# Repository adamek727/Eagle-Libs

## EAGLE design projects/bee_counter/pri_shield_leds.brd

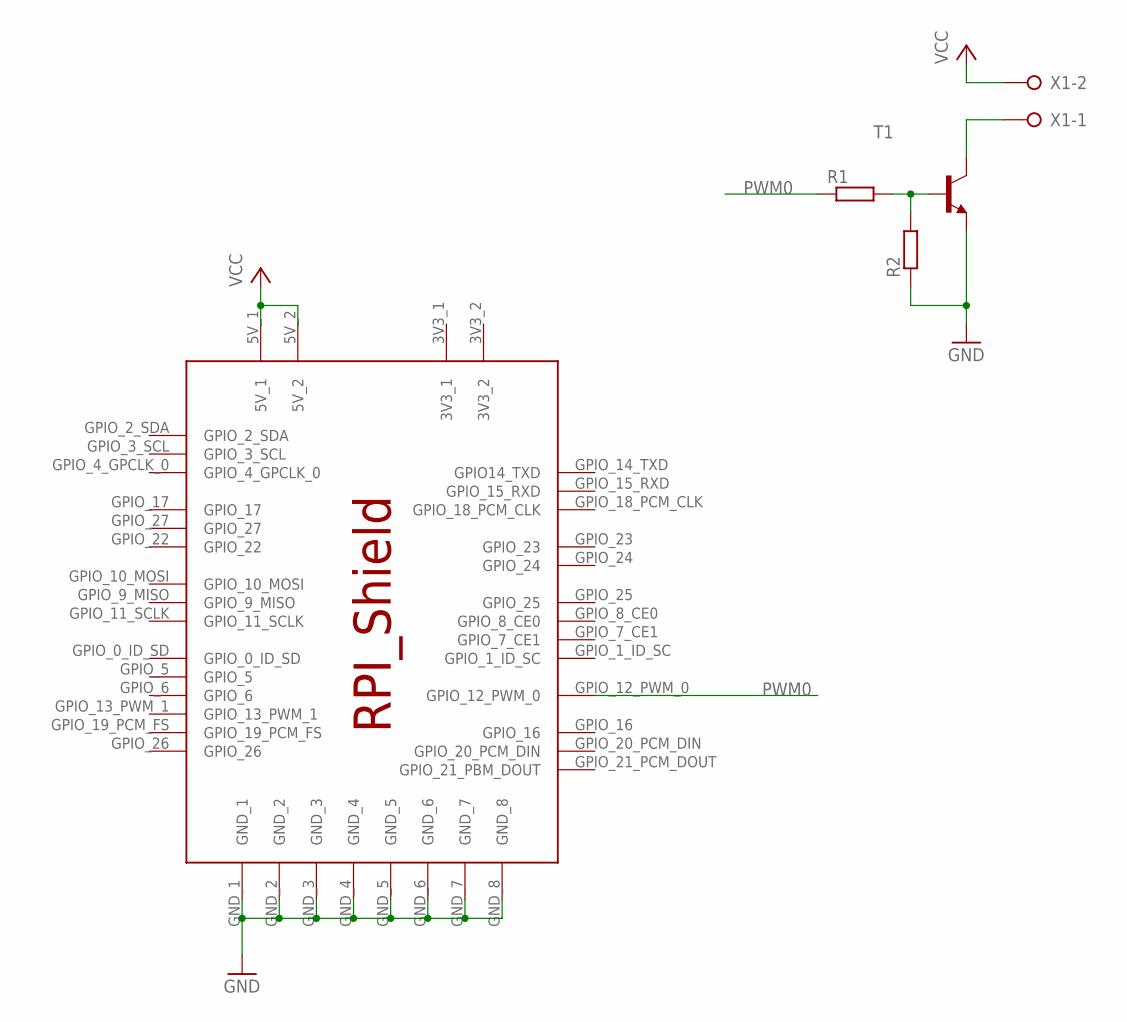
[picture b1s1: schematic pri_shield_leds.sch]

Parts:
R1, R2: R-EU_R1206; R1206
T1: -NPN-SOT223; SOT223
U$1: RPI_SHIELD
X1: W237-02P; W237-132

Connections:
GND: R2.1, T1.3 (E), U$1.GND_1, U$1.GND_2, U$1.GND_3, U$1.GND_4, U$1.GND_5, U$1.GND_6, U$1.GND_7, U$1.GND_8
unnamed: T1.4 (C), X1.1
unnamed: R1.2, R2.2, T1.1 (B)
PWM0: R1.1, U$1.GPIO_12_PWM_0
VCC: U$1.5V_1, U$1.5V_2, X1.2

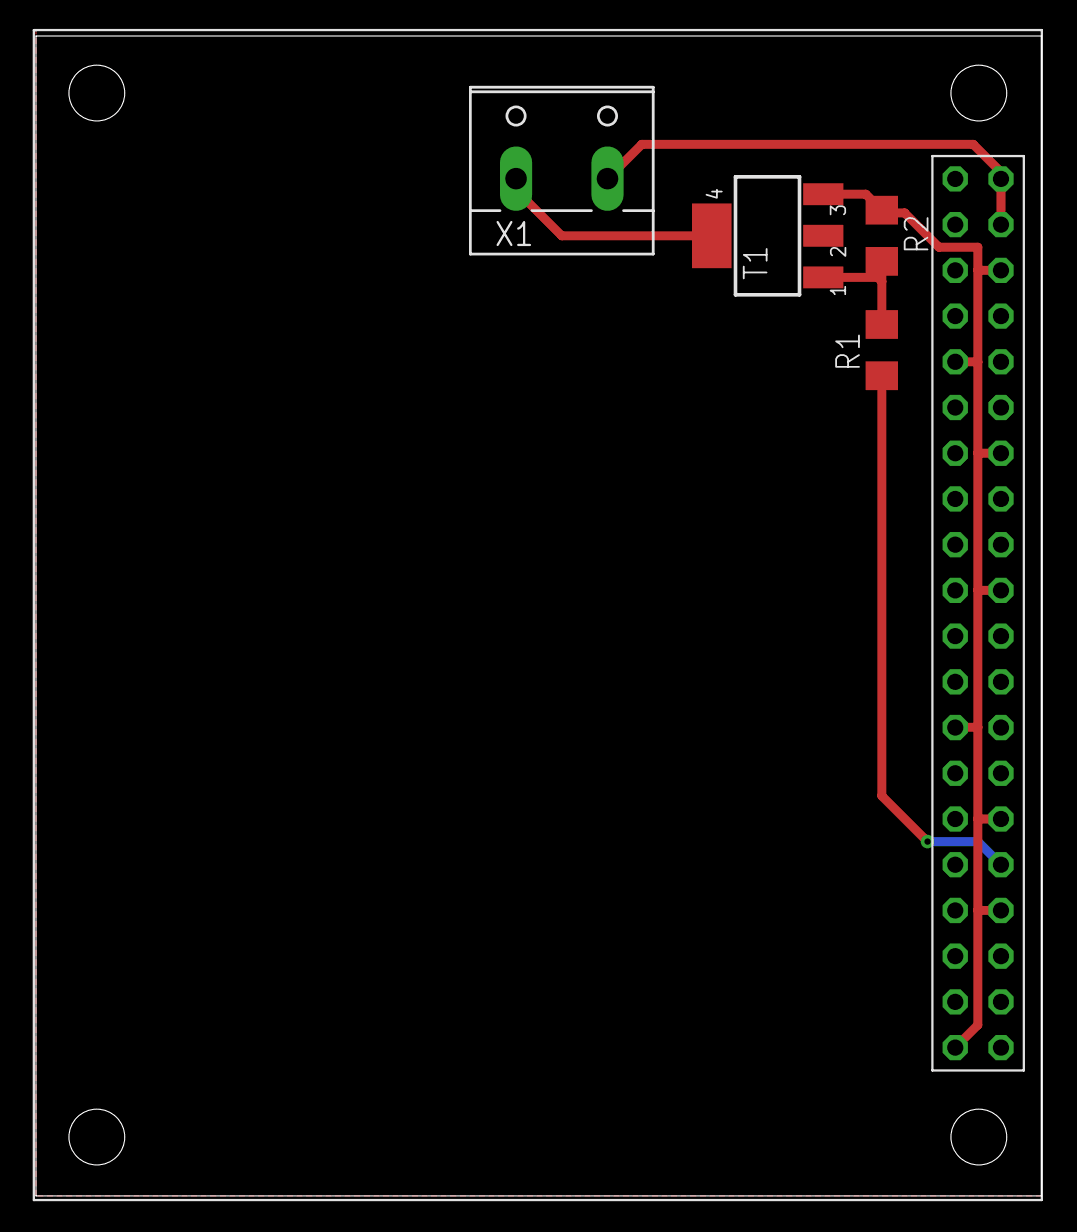
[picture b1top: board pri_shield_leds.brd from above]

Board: 2 copper layers, 55.9 x 64.4 mm, 5 parts (0 on the bottom side), 5 nets.

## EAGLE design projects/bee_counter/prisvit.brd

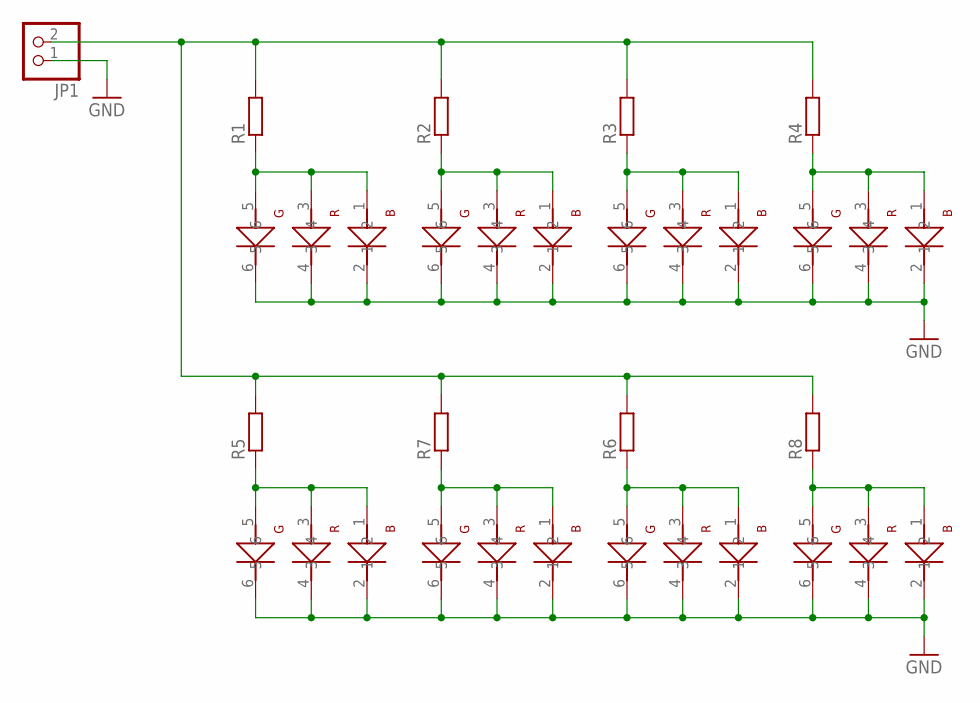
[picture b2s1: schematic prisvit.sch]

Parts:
JP1: PINHD-1X2; 1X02
R1, R2, R3, R4, R5, R6, R7, R8: R-EU_M2012; M2012
U$1, U$2, U$3, U$4, U$5, U$6, U$7, U$8: 5050_LED

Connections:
GND: JP1.1, U$1.2, U$1.4, U$1.6, U$2.2, U$2.4, U$2.6, U$3.2, U$3.4, U$3.6, U$4.2, U$4.4, U$4.6, U$5.2, U$5.4, U$5.6, U$6.2, U$6.4, U$6.6, U$7.2, U$7.4, U$7.6, U$8.2, U$8.4, U$8.6
unnamed: JP1.2, R1.2, R2.2, R3.2, R4.2, R5.2, R6.2, R7.2, R8.2
unnamed: R4.1, U$6.1, U$6.3, U$6.5
unnamed: R3.1, U$4.1, U$4.3, U$4.5
unnamed: R2.1, U$3.1, U$3.3, U$3.5
unnamed: R1.1, U$2.1, U$2.3, U$2.5
unnamed: R5.1, U$8.1, U$8.3, U$8.5
unnamed: R7.1, U$1.1, U$1.3, U$1.5
unnamed: R6.1, U$5.1, U$5.3, U$5.5
unnamed: R8.1, U$7.1, U$7.3, U$7.5

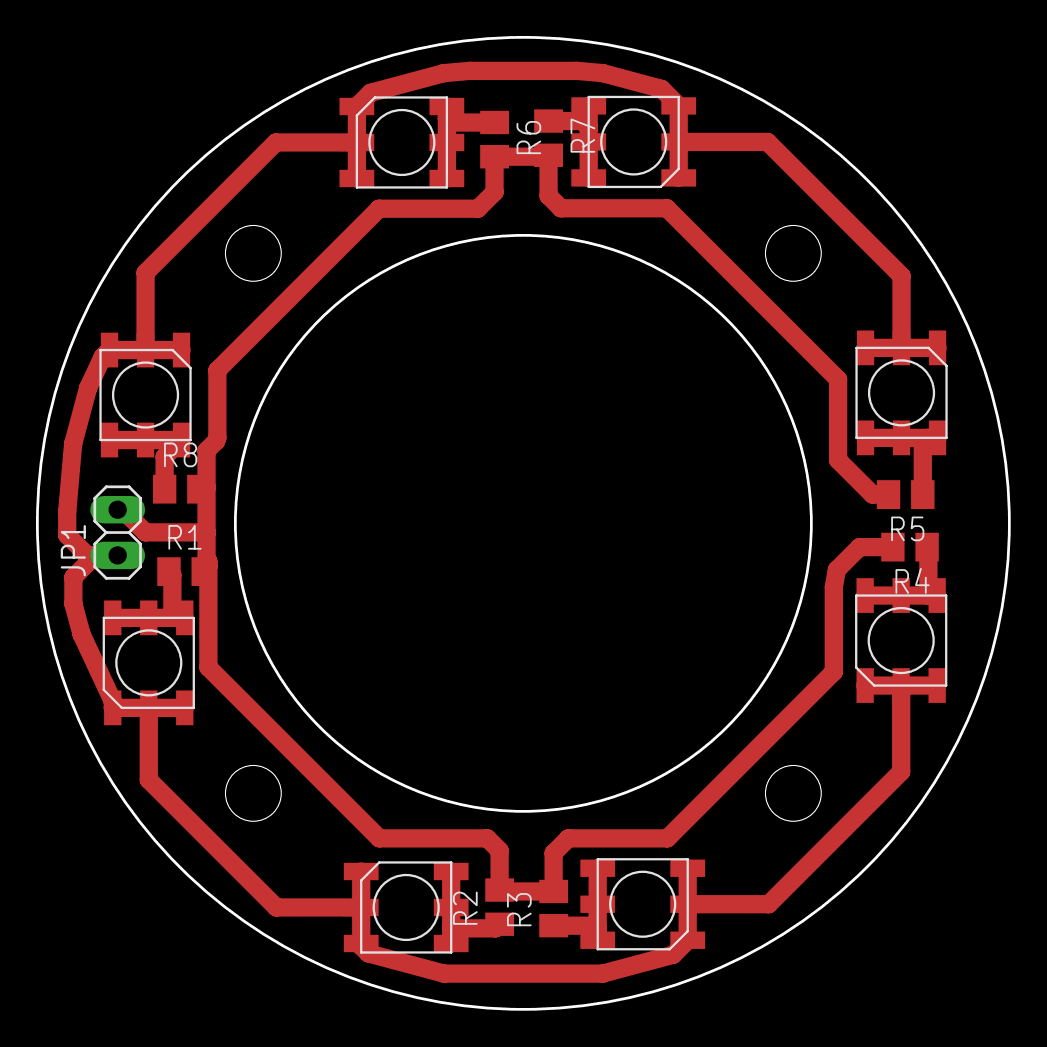
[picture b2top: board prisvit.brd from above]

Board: 2 copper layers, 54.0 x 54.0 mm, 17 parts (0 on the bottom side), 10 nets.

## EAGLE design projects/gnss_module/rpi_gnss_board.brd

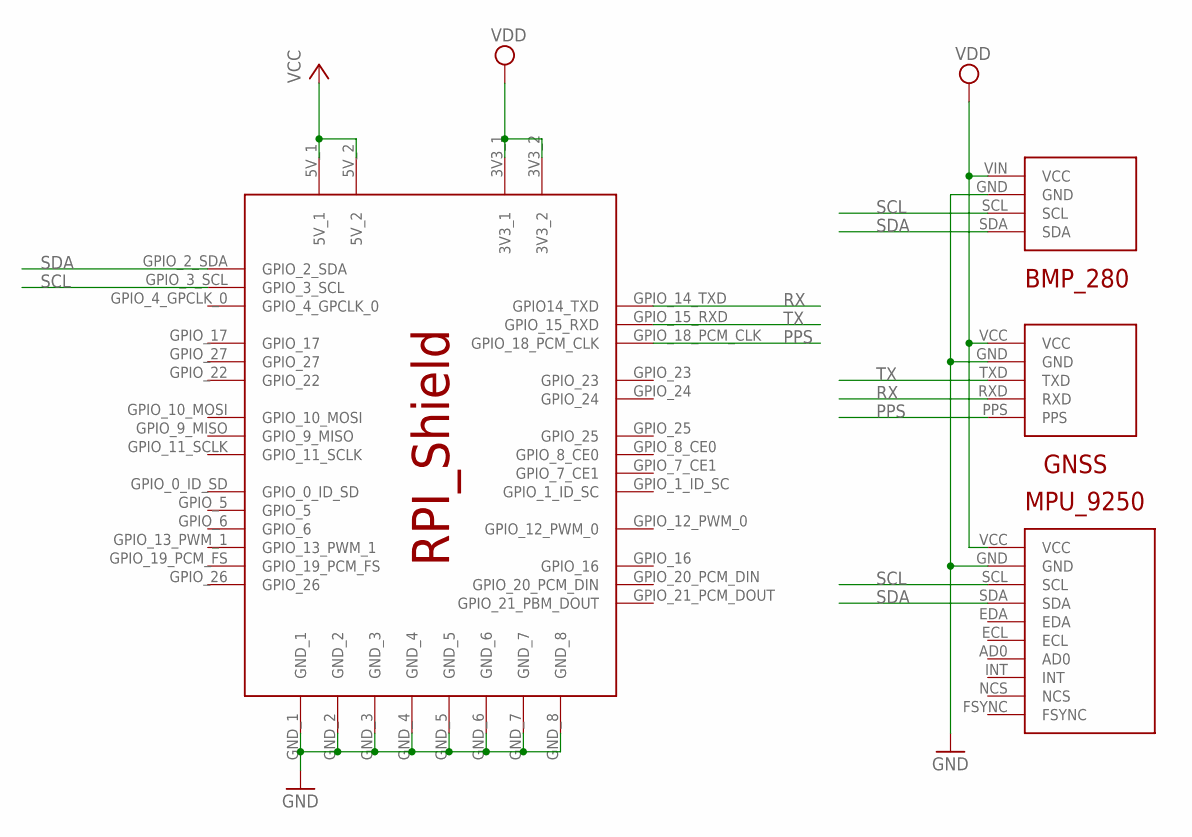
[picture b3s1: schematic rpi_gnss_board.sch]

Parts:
U$1: RPI_SHIELD
U$2: BMP_280
U$3: GNSS_MODULE_UBLOX
U$4: MPU_9250

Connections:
GND: U$1.GND_1, U$1.GND_2, U$1.GND_3, U$1.GND_4, U$1.GND_5, U$1.GND_6, U$1.GND_7, U$1.GND_8, U$2.GND, U$3.GND, U$4.GND
PPS: U$1.GPIO_18_PCM_CLK, U$3.PPS
RX: U$1.GPIO_14_TXD (GPIO14_TXD), U$3.RXD
SCL: U$1.GPIO_3_SCL, U$2.SCL, U$4.SCL
SDA: U$1.GPIO_2_SDA, U$2.SDA, U$4.SDA
TX: U$1.GPIO_15_RXD, U$3.TXD
VCC: U$1.5V_1, U$1.5V_2
VDD: U$1.3V3_1, U$1.3V3_2, U$2.VIN (VCC), U$3.VCC, U$4.VCC

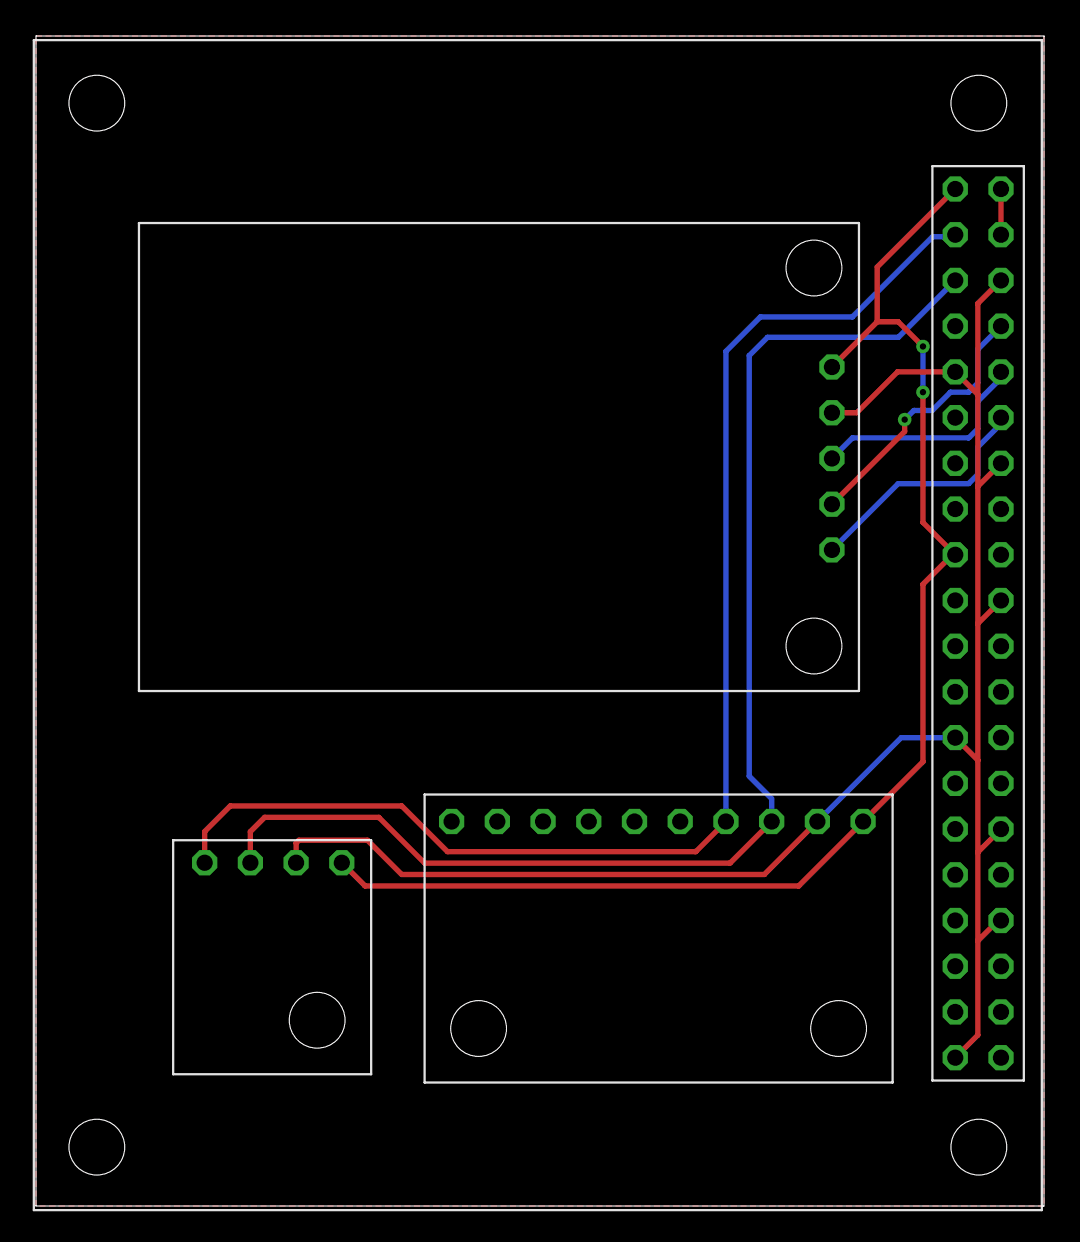
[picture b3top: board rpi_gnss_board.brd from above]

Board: 2 copper layers, 56.0 x 65.0 mm, 4 parts (0 on the bottom side), 8 nets.

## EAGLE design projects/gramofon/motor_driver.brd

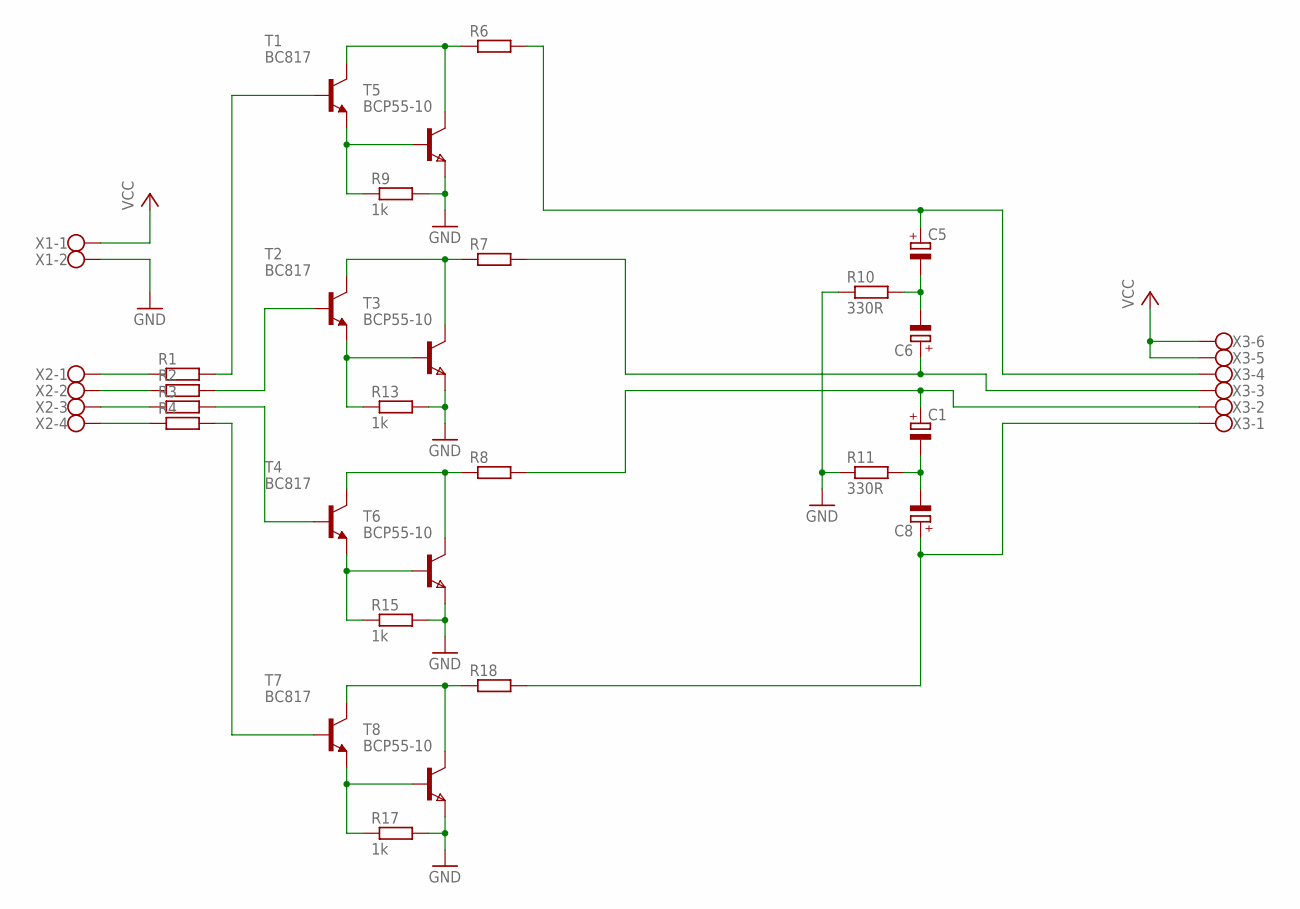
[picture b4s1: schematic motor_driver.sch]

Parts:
C1, C5, C6, C8: CPOL-EU153CLV-0807; 153CLV-0807
R1, R2, R3, R4: R-EU_M1206; M1206
R6, R7, R8, R18: R-EU_0922/22; 0922/22
R9, R13, R15, R17: 1k; M1206
R10, R11: 330R; M1206
T1, T2, T4, T7: BC817; SOT23-BEC
T3, T5, T6, T8: BCP55-10; SOT223
X1: W237-102
X2: W237-4
X3: W237-6

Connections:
GND: R9.2, R10.1, R11.1, R13.2, R15.2, R17.2, T3.3 (E), T5.3 (E), T6.3 (E), T8.3 (E), X1.2
unnamed: R1.1, X2.1
unnamed: R2.1, X2.2
unnamed: R3.1, X2.3
unnamed: R4.1, X2.4
unnamed: R1.2, T1.B
unnamed: C1.-, C8.-, R11.2
unnamed: R9.1, T1.E, T5.1 (B)
unnamed: R6.1, T1.C, T5.2 (C), T5.4 (C)
unnamed: C6.+, R7.2, X3.3
unnamed: C5.+, R6.2, X3.4
unnamed: C5.-, C6.-, R10.2
unnamed: R2.2, T2.B
unnamed: R13.1, T2.E, T3.1 (B)
unnamed: R7.1, T2.C, T3.2 (C), T3.4 (C)
unnamed: R3.2, T4.B
unnamed: R15.1, T4.E, T6.1 (B)
unnamed: R8.1, T4.C, T6.2 (C), T6.4 (C)
unnamed: C1.+, R8.2, X3.2
unnamed: R4.2, T7.B
unnamed: R17.1, T7.E, T8.1 (B)
unnamed: R18.1, T7.C, T8.2 (C), T8.4 (C)
unnamed: C8.+, R18.2, X3.1
VCC: X1.1, X3.5, X3.6

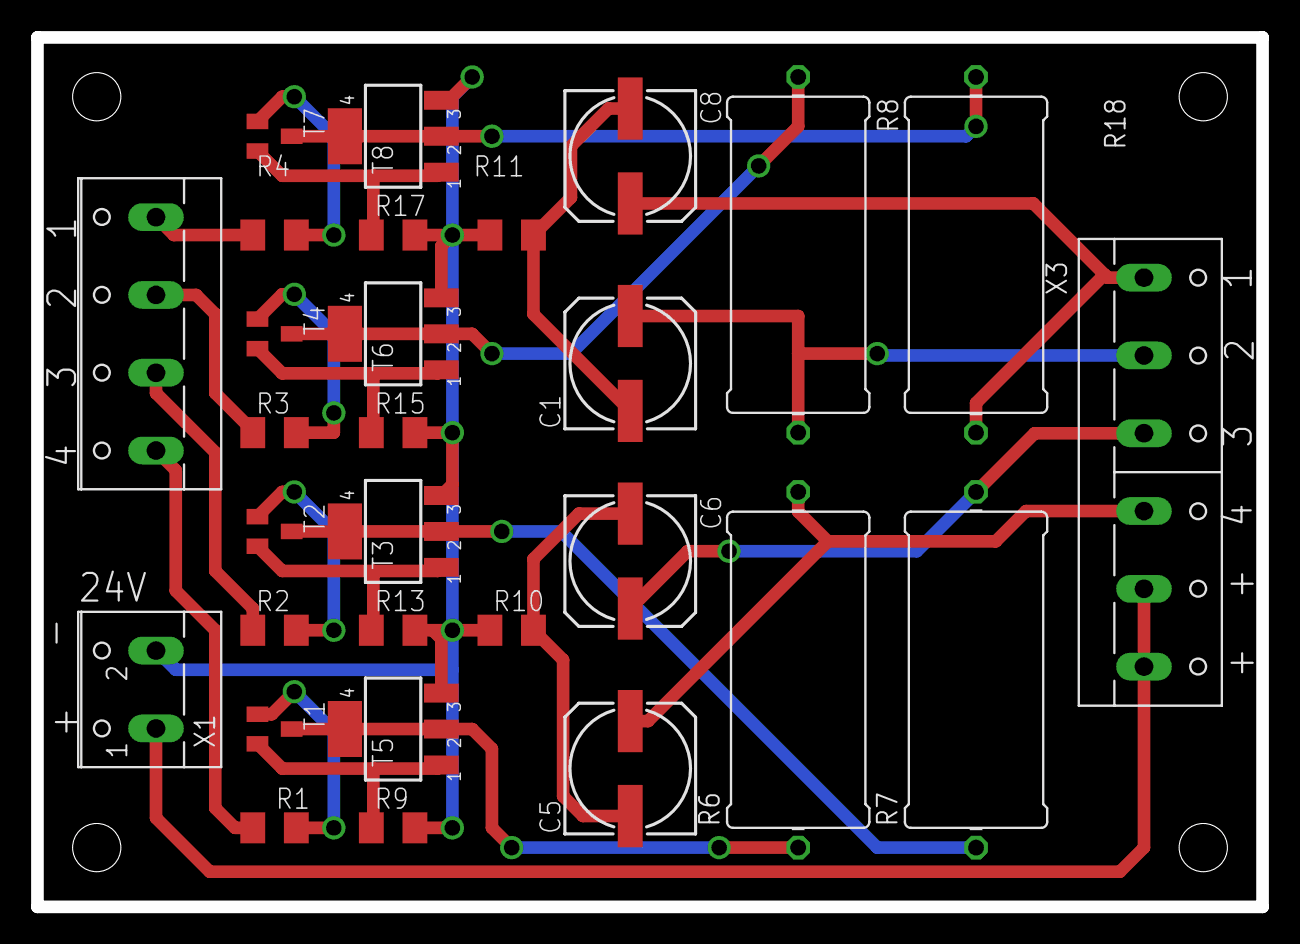
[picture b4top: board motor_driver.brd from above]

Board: 2 copper layers, 78.7 x 55.9 mm, 29 parts (0 on the bottom side), 24 nets.

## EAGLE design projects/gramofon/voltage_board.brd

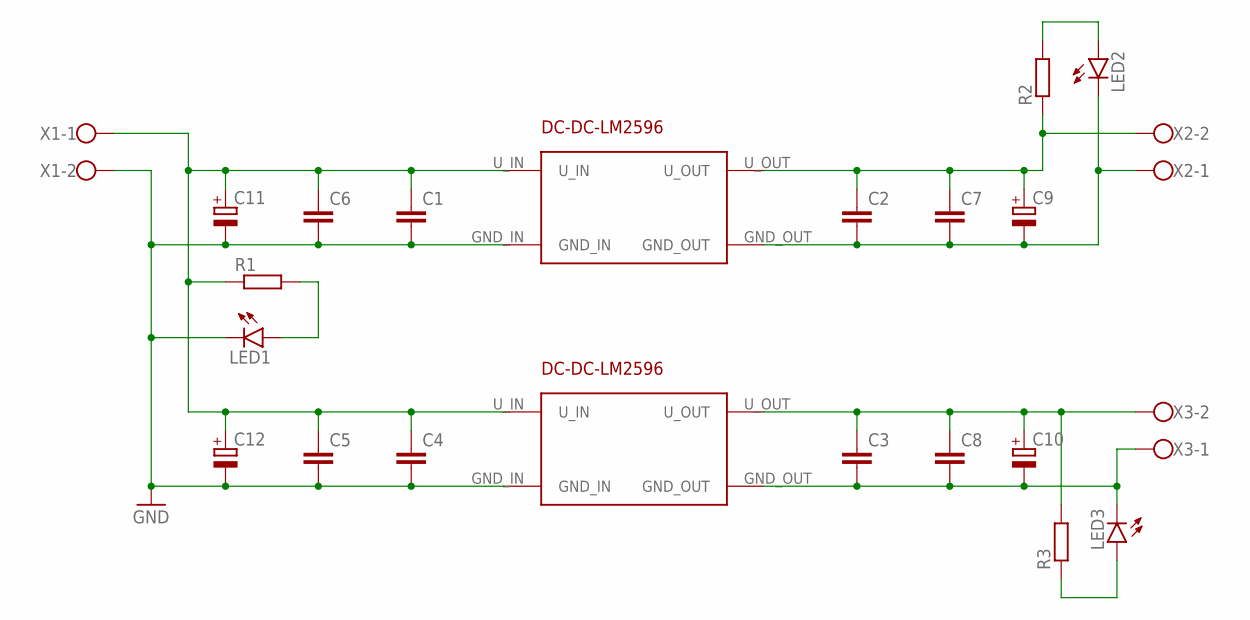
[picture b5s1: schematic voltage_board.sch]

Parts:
C1, C2, C3, C4, C5, C6, C7, C8: C-EUC1206; C1206
C9, C10, C11, C12: CPOL-EU140CLH-0810; 140CLH-0810
LED1, LED2, LED3: LEDSML1206; SML1206
R1, R2, R3: R-EU_M1206; M1206
U$1, U$2: DC-DC-LM2596
X1, X2, X3: W237-102

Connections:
GND: C1.2, C4.2, C5.2, C6.2, C11.-, C12.-, LED1.C, U$1.GND_IN, U$2.GND_IN, X1.2
unnamed: LED1.A, R1.2
unnamed: C3.2, C8.2, C10.-, LED3.C, U$2.GND_OUT, X3.1
unnamed: LED2.A, R2.2
unnamed: C3.1, C8.1, C10.+, R3.2, U$2.U_OUT, X3.2
unnamed: C1.1, C4.1, C5.1, C6.1, C11.+, C12.+, R1.1, U$1.U_IN, U$2.U_IN, X1.1
unnamed: C2.2, C7.2, C9.-, LED2.C, U$1.GND_OUT, X2.1
unnamed: C2.1, C7.1, C9.+, R2.1, U$1.U_OUT, X2.2
unnamed: LED3.A, R3.1

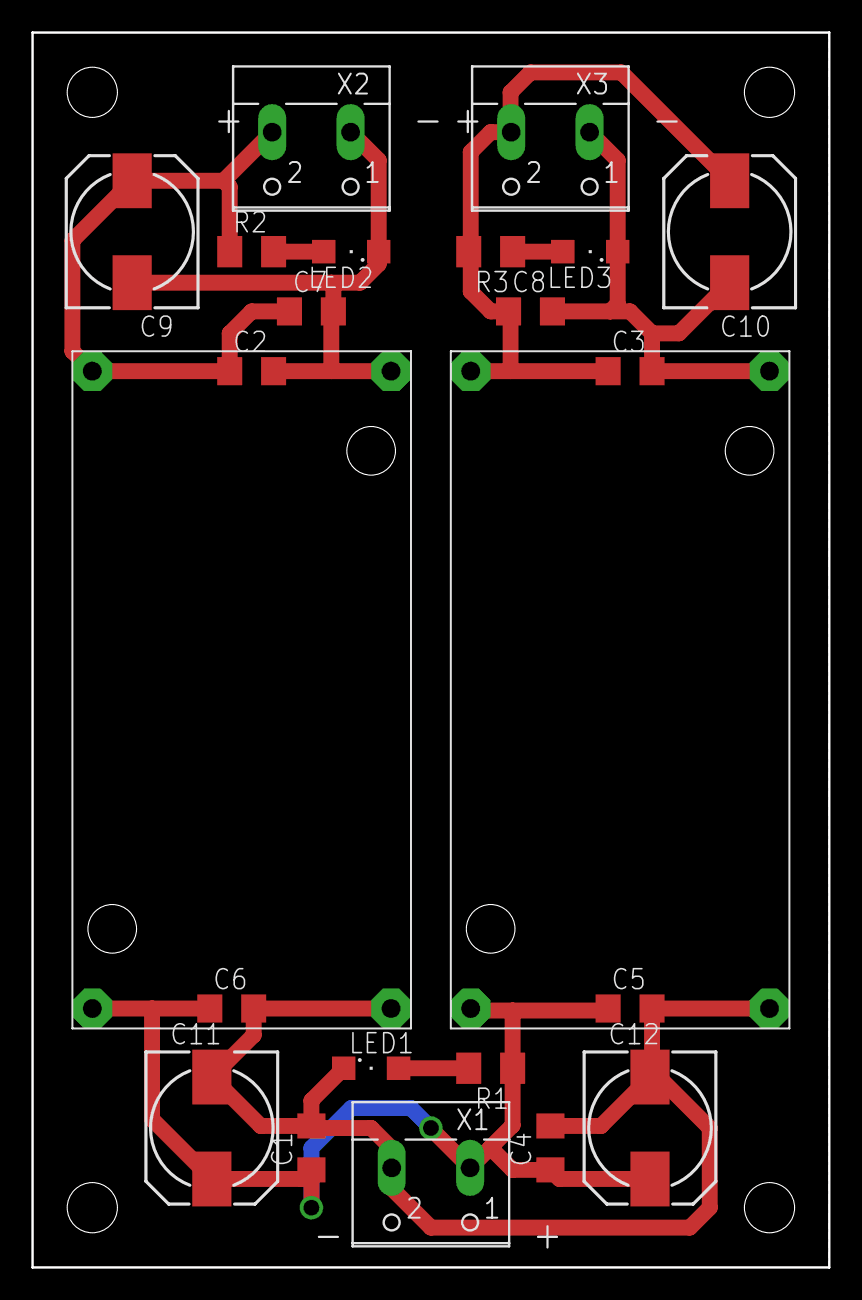
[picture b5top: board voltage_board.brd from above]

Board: 2 copper layers, 50.8 x 78.7 mm, 23 parts (0 on the bottom side), 9 nets.

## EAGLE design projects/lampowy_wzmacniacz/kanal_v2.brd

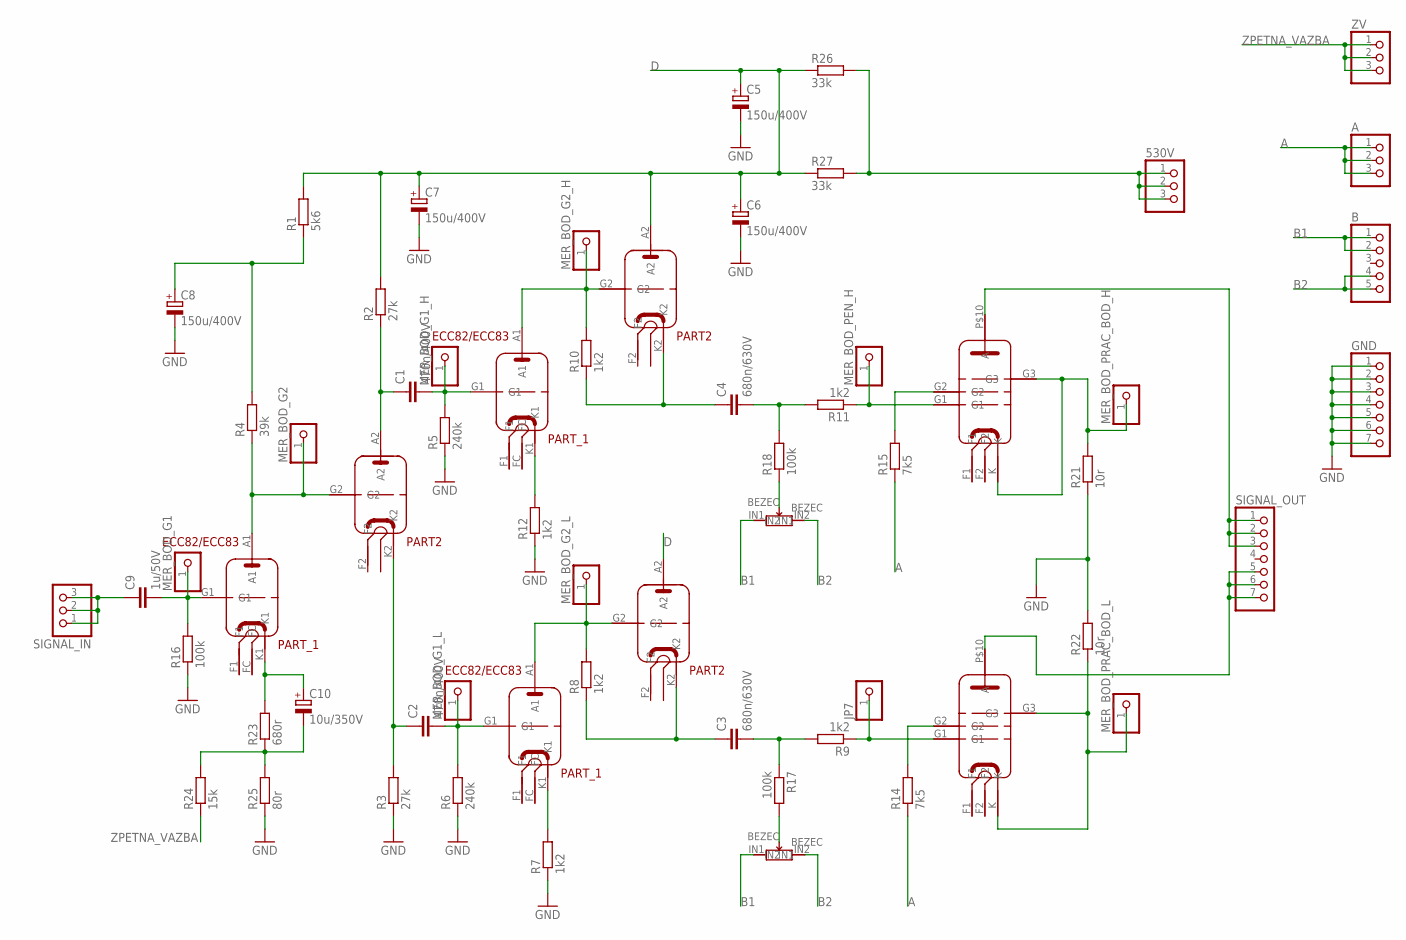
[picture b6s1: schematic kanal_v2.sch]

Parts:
530V: 1X03
A: 1X03
B: 1X05
C1, C2: 470n/400V; C15B7
C3, C4: 680n/630V; C27.5B11
C5, C6, C7, C8: 150u/400V; EB25D
C9: 1u/50V; C5B3.5
C10: 10u/350V; E5-10,5
GND: 1X07
JP7: 1X01
MER_BOD_G1, MER_BOD_G1_H, MER_BOD_G1_L, MER_BOD_G2, MER_BOD_G2_H, MER_BOD_G2_L: 1X01
MER_BOD_PEN_H: 1X01
MER_BOD_PRAC_BOD_H: 1X01
MER_BOD_PRAC_BOD_L: 1X01
R1: 5k6; 0309/10
R2, R3: 27k; 0309/10
R4: 39k; 0309/10
R5, R6: 240k; 0309/10
R7, R8, R9, R10, R11, R12: 1k2; 0309/10
R14, R15: 7k5; 0309/10
R16, R17, R18: 100k; 0309/10
R21, R22: 10r; 0309/10
R23: 680r; 0309/10
R24: 15k; 0309/10
R25: 80r; 0309/10
R26, R27: 33k; 0309/10
SIGNAL_IN: 1X03
SIGNAL_OUT: 1X07
U$1: ECC82; ECC82_PACKAGE
U$2, U$3: ECC83; ECC82_PACKAGE
U$4, U$5: PL509; PL509_PACKAGE
U$6, U$7: TRIMMER; TRIMMER_15X15_PACKAGE
ZV: 1X03

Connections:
A: A.1, A.2, A.3, R14.1, R15.1
B1: B.1, B.2, U$6.IN1, U$7.IN1
B2: B.4, B.5, U$6.IN2, U$7.IN2
D: C5.+, C6.+, C7.+, R1.2, R2.2, R26.1, R27.1, U$2.A2, U$3.A2
GND: C5.-, C6.-, C7.-, C8.-, GND.1, GND.2, GND.3, GND.4, GND.5, GND.6, GND.7, R3.1, R5.1, R6.1, R7.1, R12.1, R16.1, R21.1, R22.2, R25.1
MER_BOD_PEN_L: JP7.1, R9.1, U$5.G1
unnamed: C9.2, MER_BOD_G1.1, R16.2, U$1.G1
unnamed: C10.+, R23.2, U$1.K1
unnamed: C10.-, R23.1, R24.2, R25.2
unnamed: MER_BOD_G2.1, R4.1, U$1.A1, U$1.G2
unnamed: C8.+, R1.1, R4.2
unnamed: C1.1, R2.1, U$1.A2
unnamed: C2.1, R3.2, U$1.K2
unnamed: C1.2, MER_BOD_G1_H.1, R5.2, U$2.G1
unnamed: C2.2, MER_BOD_G1_L.1, R6.2, U$3.G1
unnamed: R17.2, U$6.BEZEC
unnamed: R7.2, U$3.K1
unnamed: MER_BOD_G2_L.1, R8.2, U$3.A1, U$3.G2
unnamed: C3.1, R8.1, U$3.K2
unnamed: C3.2, R9.2, R17.1
unnamed: R14.2, U$5.G2
unnamed: C4.1, R10.1, U$2.K2
unnamed: MER_BOD_PRAC_BOD_L.1, R22.1, U$5.G3, U$5.K
unnamed: MER_BOD_PRAC_BOD_H.1, R21.2, U$4.G3, U$4.K
unnamed: MER_BOD_G2_H.1, R10.2, U$2.A1, U$2.G2
unnamed: SIGNAL_OUT.5, SIGNAL_OUT.6, SIGNAL_OUT.7, U$5.P$10 (A)
unnamed: 530V.1, 530V.2, 530V.3, R26.2, R27.2
unnamed: C4.2, R11.2, R18.2
unnamed: MER_BOD_PEN_H.1, R11.1, U$4.G1
unnamed: R18.1, U$7.BEZEC
unnamed: R12.2, U$2.K1
unnamed: C9.1, SIGNAL_IN.1, SIGNAL_IN.2, SIGNAL_IN.3
unnamed: R15.2, U$4.G2
unnamed: SIGNAL_OUT.1, SIGNAL_OUT.2, SIGNAL_OUT.3, U$4.P$10 (A)
ZPETNA_VAZBA: R24.1, ZV.1, ZV.2, ZV.3

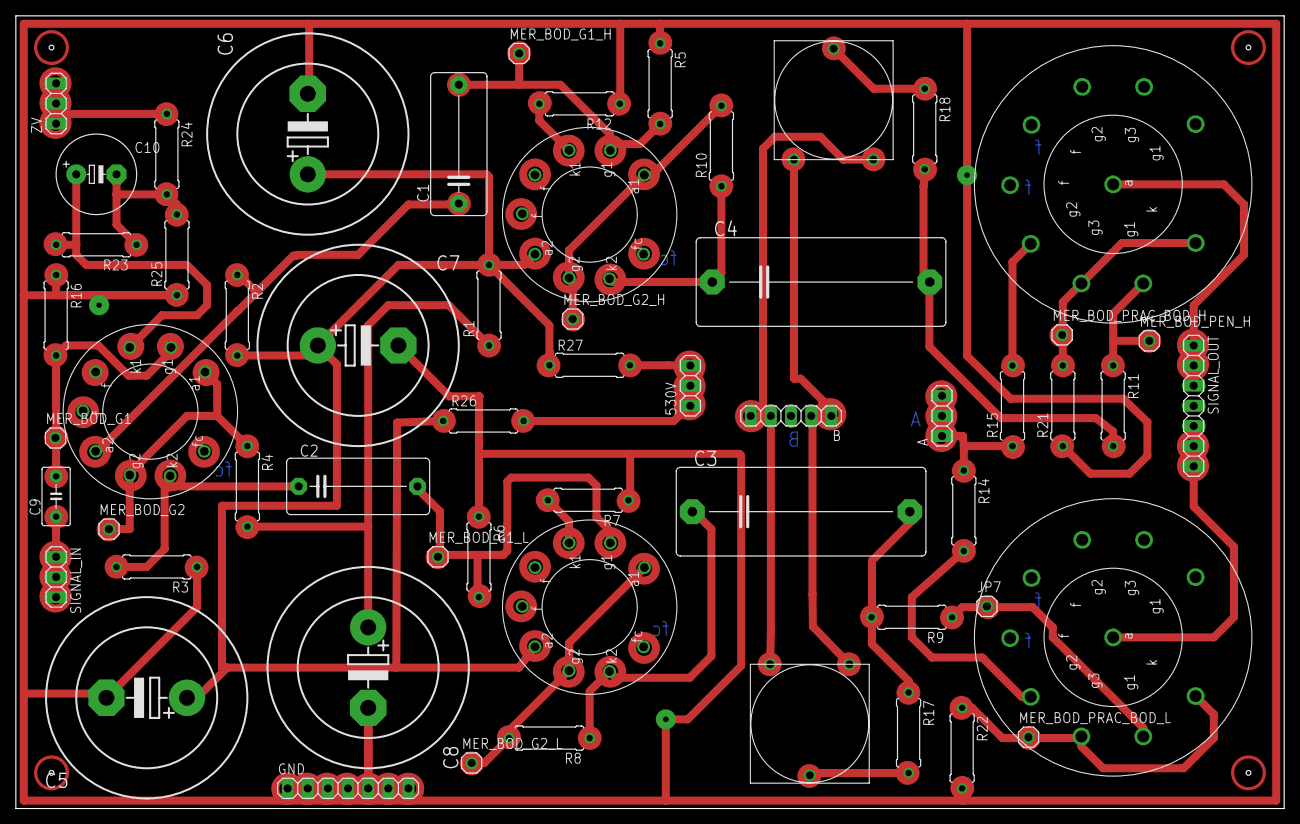
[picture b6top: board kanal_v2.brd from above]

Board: 2 copper layers, 160.0 x 100.0 mm, 58 parts (0 on the bottom side), 35 nets.

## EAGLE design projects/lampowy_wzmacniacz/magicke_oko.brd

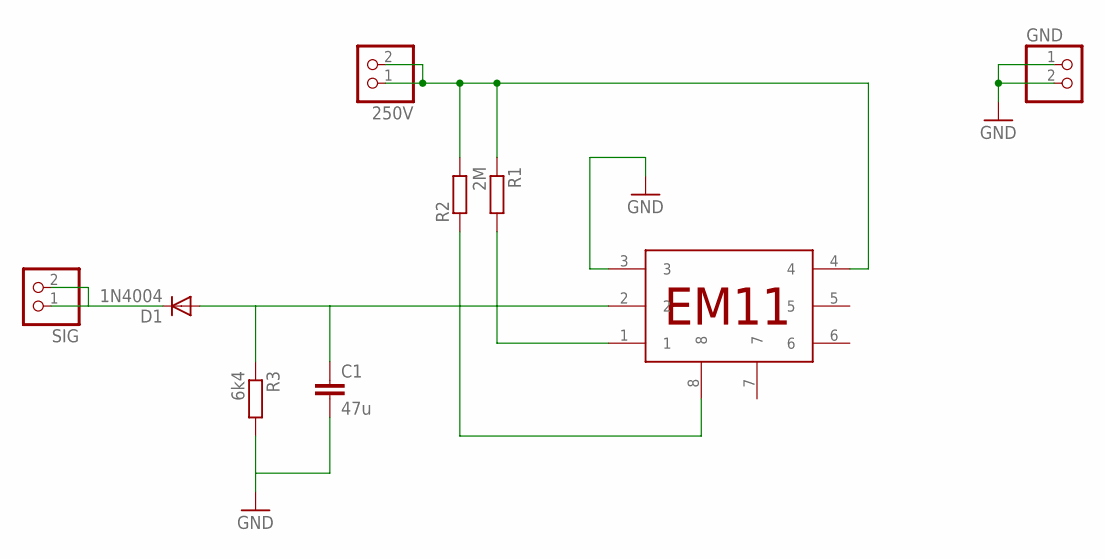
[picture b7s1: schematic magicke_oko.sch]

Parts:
250V: PINHD-1X2; 1X02
C1: 47u; C050-075X075
D1: 1N4004; DO41-10
GND: PINHD-1X2; 1X02
R1: 2M; 0309/10
R2: R-EU_0309/10; 0309/10
R3: 6k4; 0309/10
SIG: PINHD-1X2; 1X02
U$1: EM11; EM11_PACKAGE

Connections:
GND: C1.2, GND.1, GND.2, R3.2, U$1.3
unnamed: R1.2, U$1.1
unnamed: D1.C, SIG.1, SIG.2
unnamed: 250V.1, 250V.2, R1.1, R2.2, U$1.4
unnamed: C1.1, D1.A, R3.1, U$1.2
unnamed: R2.1, U$1.8

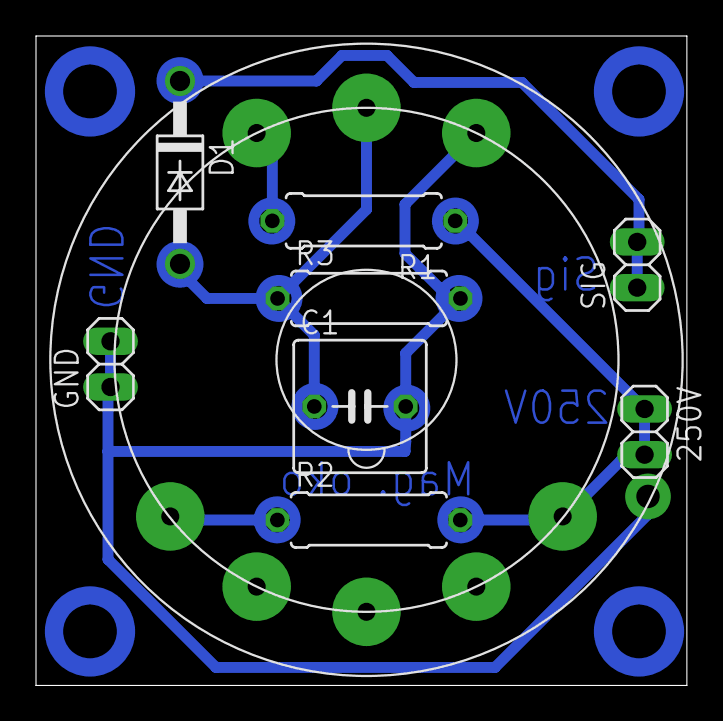
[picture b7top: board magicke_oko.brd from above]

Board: 2 copper layers, 36.2 x 36.1 mm, 9 parts (0 on the bottom side), 6 nets.

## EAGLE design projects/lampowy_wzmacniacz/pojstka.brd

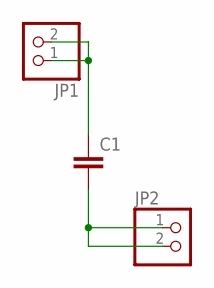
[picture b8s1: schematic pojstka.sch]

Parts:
C1: C-EU225-087X268; C225-087X268
JP1, JP2: PINHD-1X2; 1X02

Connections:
unnamed: C1.1, JP1.1, JP1.2
unnamed: C1.2, JP2.1, JP2.2

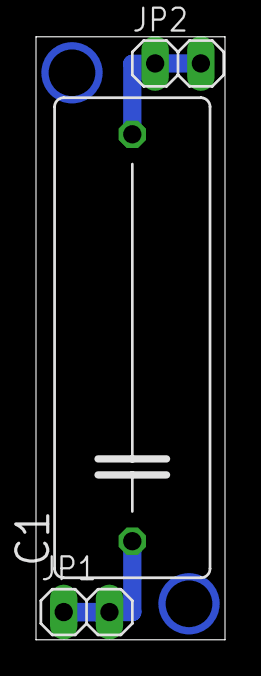
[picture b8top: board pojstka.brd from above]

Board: 2 copper layers, 10.5 x 33.5 mm, 3 parts (0 on the bottom side), 2 nets.
